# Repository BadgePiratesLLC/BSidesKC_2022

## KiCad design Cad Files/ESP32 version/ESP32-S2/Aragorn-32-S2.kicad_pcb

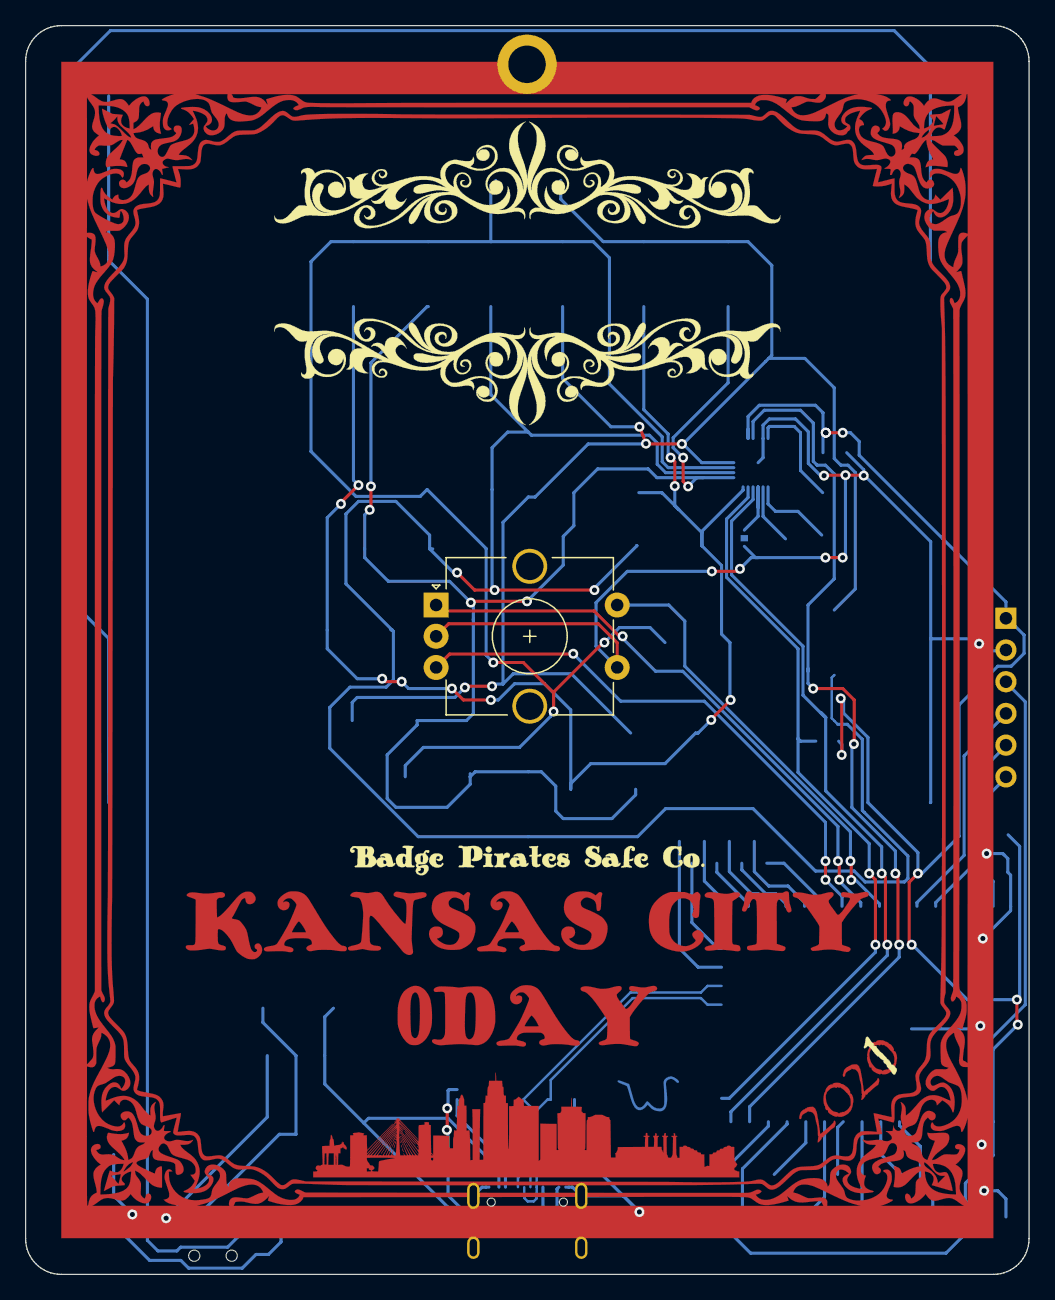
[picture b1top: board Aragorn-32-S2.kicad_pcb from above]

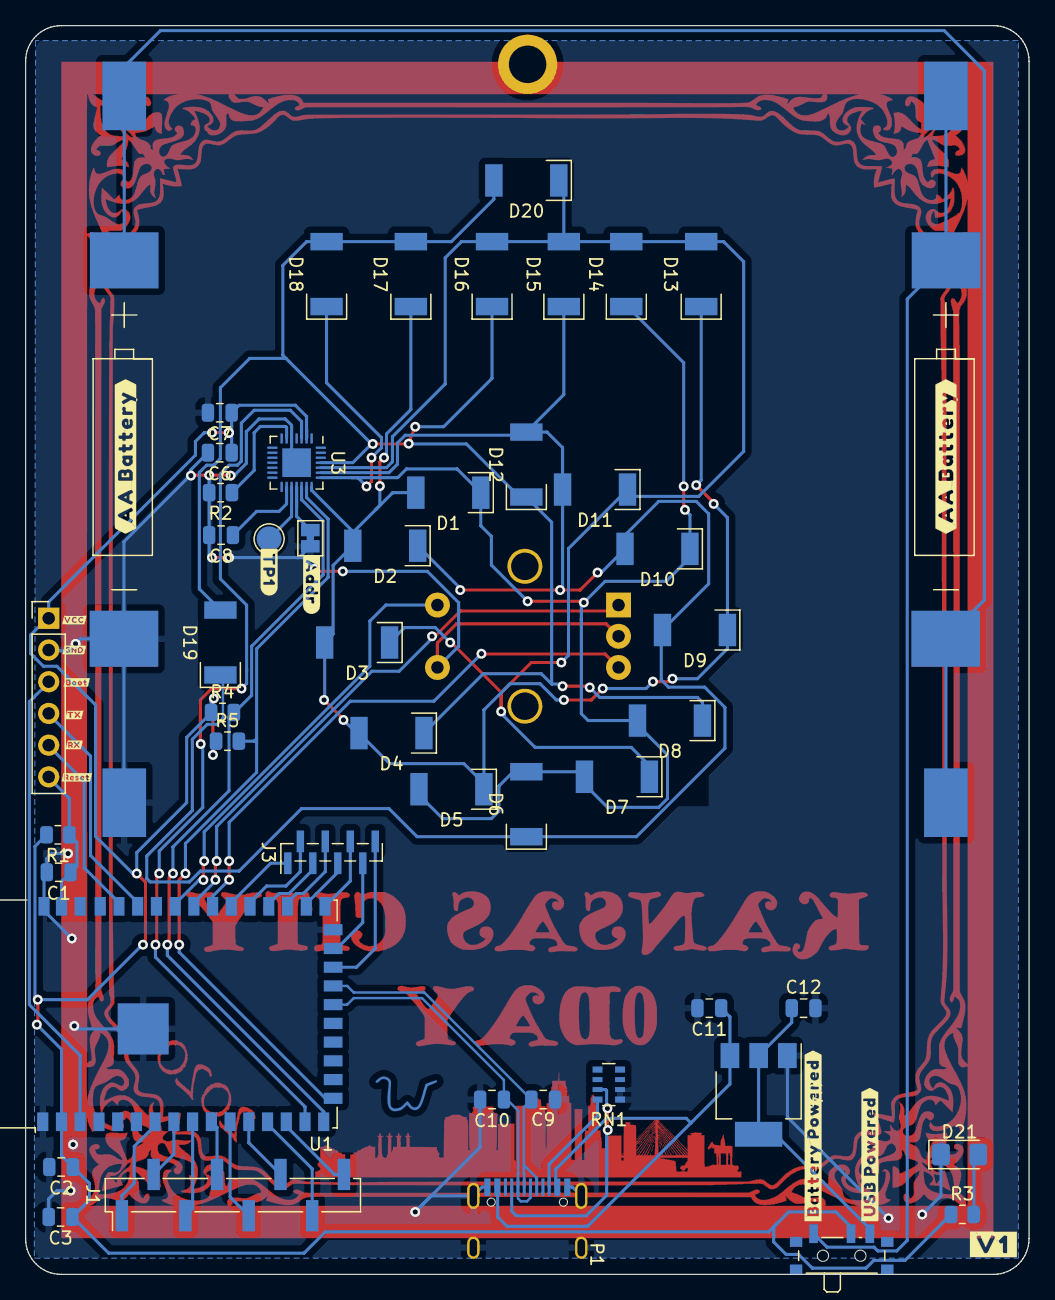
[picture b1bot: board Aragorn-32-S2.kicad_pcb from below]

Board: 2 copper layers, 80.4 x 100.0 mm, 51 parts (50 on the bottom side), 46 nets.

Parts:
BT1, BT2: Battery_Cell; AA Single
C1, C2: 100nF; C_0805_2012Metric
C3: 22uF; C_0805_2012Metric
C6, C11, C12: 1uF; C_0805_2012Metric
C7, C8: 0.1uF; C_0805_2012Metric
C9, C10: 20pF; C_0805_2012Metric
D1, D2, D3, D4, D5, D6, D7, D8, D9, D10, D11, D12, D13, D14, D15, D16, D17, D18, D19, D20: LED; XZMDK45WT-ReverseMountLED
D21: POWER; LED_1206_3216Metric_Pad1.42x1.75mm_HandSolder
J1: Conn_01x08; PinHeader_1x08_P2.54mm_Vertical_SMD_Pin1Left
J2: Program; PinHeader_1x06_P2.54mm_Vertical
J3: Conn_01x08; PinHeader_1x08_P1.00mm_Vertical_SMD_Pin1Left
JP1: ADDR; SolderJumper-2_P1.3mm_Bridged_Pad1.0x1.5mm
P1: USB_C_Plug_corrected; USB_C_Receptical-Jing
R1: 1k; R_0805_2012Metric
R2: 20k; R_0805_2012Metric
R3: R; R_0805_2012Metric
R4, R5: 10k; R_0805_2012Metric
RN1: 5.1k; R_Array_Convex_4x0603
Ref**: Val**; W
SW1: Rotary_Encoder_Switch; RotaryEncoder_Alps_EC12E-Switch_Vertical_H20mm_CircularMoun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
SW2: SW_SPDT; SW_SPDT_PCM12
TP1: AIN; TestPoint_Pad_D2.0mm
U1: ESP32-S2-WROVER
U3: IS31FL3731-QF; QFN-28-1EP_4x4mm_P0.4mm_EP2.3x2.3mm
U4: TLV1117-33; SOT-223-3_TabPin2

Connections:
/ESP32-S2/D+: C9.1, P1.A6 (D+), P1.B6 (D+), U1.23 (USB_D+)
/ESP32-S2/D-: C10.1, P1.A7 (D-), P1.B7 (D-), U1.22 (USB_D-)
/ESP32-S2/RoteryA: SW1.A, U1.34 (IO40)
/ESP32-S2/RoteryB: SW1.B, U1.33 (IO39)
/ESP32-S2/RoteryButton: SW1.S1, U1.35 (IO41)
/ESP32-S2/SCL: R5.2, U1.17 (IO14), U3.20 (SCL)
/ESP32-S2/SDA: R4.2, U1.16 (IO13), U3.19 (SDA)
/ESP32-S2/SDB: U1.15 (IO12), U3.3 (~SDB)
/Peripherals/CA1: D1.2 (A), D2.2 (A), D3.2 (A), D4.2 (A), D5.1 (K), D9.1 (K), D13.1 (K), D17.1 (K), U3.21 (CA1)
/Peripherals/CA2: D1.1 (K), D5.2 (A), D6.2 (A), D7.2 (A), D8.2 (A), D10.1 (K), D14.1 (K), D18.1 (K), U3.22 (CA2)
/Peripherals/CA3: D2.1 (K), D6.1 (K), D9.2 (A), D10.2 (A), D11.2 (A), D12.2 (A), D15.1 (K), D19.1 (K), U3.23 (CA3)
/Peripherals/CA4: D3.1 (K), D7.1 (K), D11.1 (K), D13.2 (A), D14.2 (A), D15.2 (A), D16.2 (A), D20.1 (K), U3.24 (CA4)
/Peripherals/CA5: D4.1 (K), D8.1 (K), D12.1 (K), D16.1 (K), D17.2 (A), D18.2 (A), D19.2 (A), D20.2 (A), U3.25 (CA5)
Boot: J2.3, U1.3 (IO00)
GND: BT2.2 (-), C1.2, C2.2, C3.2, C6.2, C7.2, C8.2, C9.2, C10.2, C11.2, C12.2, D21.1 (K), J2.2, JP1.1, P1.A1 (GND), P1.A12 (GND), P1.B1 (GND), P1.B12 (GND), P1.S1 (SHIELD), R2.2, RN1.1 (R1.1), RN1.2 (R2.1), SW1.C, SW1.S2, U1.1 (GND), U1.26 (GND), U1.42 (GND), U1.43 (GND), U3.5 (GND), U3.29 (GND), U4.1 (GND)
unnamed: BT1.1 (+), SW2.1 (A)
unnamed: BT1.2 (-), BT2.1 (+)
unnamed: C8.1, U3.16 (C_FILT)
unnamed: C12.1, SW2.3 (C), U4.2 (VO)
unnamed: D21.2 (A), R3.2
unnamed: J1.1, U1.7 (IO04)
unnamed: J1.2, U1.8 (IO05)
unnamed: J1.3, U1.9 (IO06)
unnamed: J1.4, U1.10 (IO07)
unnamed: J1.5, U1.11 (IO08)
unnamed: J1.6, U1.12 (IO09)
unnamed: J1.7, U1.13 (IO10)
unnamed: J1.8, U1.14 (IO11)
unnamed: J3.1, U1.32 (IO38)
unnamed: J3.2, U1.31 (IO37)
unnamed: J3.3, U1.30 (IO36)
unnamed: J3.4, U1.29 (IO35)
unnamed: J3.5, U1.28 (IO34)
unnamed: J3.6, U1.27 (IO33)
unnamed: J3.7, U1.25 (IO26)
unnamed: J3.8, U1.24 (IO21)
unnamed: JP1.2, U3.18 (AD)
unnamed: P1.A5 (CC), RN1.7 (R2.2)
unnamed: P1.B5 (VCONN), RN1.8 (R1.2)
unnamed: R2.1, U3.6 (R_EXT)
unnamed: TP1.1, U3.17 (IN)
RX: J2.5, U1.38 (RXD0)
Reset: C1.1, J2.6, R1.1, U1.41 (EN)
TX: J2.4, U1.37 (TXD0)
VBUS: C11.1, P1.A4 (VBUS), P1.A9 (VBUS), P1.B4 (VBUS), P1.B9 (VBUS), U4.3 (VI)
VCC: C2.1, C3.1, C6.1, C7.1, J2.1, R1.2, R3.1, R4.1, R5.1, SW2.2 (B), U1.2 (3V3), U3.2 (VCC)
